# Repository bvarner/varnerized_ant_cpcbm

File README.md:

# Varnerized ANT Compact PCB Maker

Since first coming across the [ANT](https://www.youtube.com/channel/UCX44z-SSL7LzcB4xxgUdHHA) project, I've wanted to make one. However there are some esoteric hardware choices in the base project that seem to prioritize form over function and cost.
As a hobbiest, my primary concerns are not asthetics as much as cost and component availability.

## Varnerizations
1. Created a parametric (parameterized) reimplemenation of the [bridge & head in Fusion 360](https://a360.co/3jG9QqE). Fusion Archive and STEP export included.
2. 8MM Linear Rods & LM8UU linear bearings. 
    * Sacrificed 4mm of Y axis travel to allow for wall thicknesses to be reasonable with 15mm bores.
    * Added 1mm to the height to the left-right bridge and center bridge, added 1mm separation betweeen centers of the x-axis rails.
3. Bridge Core is now One Piece.
    * Captive M3 Hex Nuts allow the use of (3) M3x30 and (3) M3x40 screws instead of the original BOM spec for (3) M3 threaded rods cut to length.
    * Linear bearing holes are _barely_ oversized, allowing for the M3x30 screws to act as compression mechanisms to hold the bearings.
    * Expansion / Compression cut for linear bearings. M3 screws holding together the bridge act as compression points to hold the bearings snug.
4. Use of sub-mini microswitches for limit-switches. No need to purchase specific orientation limit switch modules, especially when the connections to the grbl board aren't making use of pull resistors.
5. NEMA17 Stepper Motors
    * Reinforced COREXY Mounts based upon [this design on Thingiverse](https://www.thingiverse.com/thing:3590519) eliminate the need for extra retainers from the thingiverse part.
    * GT2 belt-driven Z-Axis. [140 Tooth 2GT-6](https://www.amazon.com/140-2GT-6-Timing-Belt-Closed-Loop/dp/B014QJBVOY/ref=sr_1_2?dchild=1&keywords=GT2-140+belt&qid=1634881957&qsid=135-9090533-9887601&sr=8-2&sres=B014QJBVOY%2CB014SLWP68%2CB07B5ZQY4W%2CB096D4NTVR%2CB07MWDMBWK%2CB01HM6DIA8%2CB07X9CHY23%2CB07KK86NYX%2CB0897CJKS1%2CB01IPYNQT4%2CB01E91K4N8%2CB08BJ2G2X6%2CB00XR0YJIO%2CB08974S1CC%2CB07JKT5BZQ%2CB00OZDJTKK) allows for swapping out gear ratios to adjust for different leadscrew pitches.
6. TR8 Leadscrew (with 8mm pitch) for Z-Axis
7. Remodeled and removed unnecessary holes from the bridge left and right.
8. Belt holder holds a captive nut to secure it to the bridge.
9. Easily Obtainable [D2826 1000kv](https://www.amazon.com/dp/B089YPSYD6?psc=1&ref=ppx_yo2_dt_b_product_details) BLDC motor.
    * 3d-printed TPU (shore 95A) drive belt.
    * 3d-printed PolyCarbonate drive pulleys. (Eliminated the stop-collar on the spindle)
10. Use of an open cable chain, and necessary mounts to the bridge & electronics case.
    * Use of 40mm screws on the electronics case, further customizations to make it easier to fit panel-mount through-hole jacks.
    * modified the electronics panel to use a rectangular switch and a XT-60H connector for power.
11. 3d printed GT2 pulleys.
    * I have since switched to machine pulleys, as I was diagnosing some movement precision issues. Changing to machined pulleys had no noticeable effect. My issues were elsewhere.
12. PCBLock <-> Frame connection.
    * Changed orientation of the contact strips to vertical -- allowing for more 'slop' between alignment in both the x, and z axis.
    * Contact is no longer dependent upon the thickness of the spoil-board, so thinner / thicker board will still contact well.
    * I used 4mm strips of 0.15mm thick nickel strip. (cut from an 8mm wide strip commonly used in 18650 battery packs)

### Analysis and Evaulation Guidelines

In making my decisions about what to 'Varnerize' vs. purchase and stick to the plans I weighed things based upon:

* What's already in my component drawers or easily obtainable given current supply chain and production limitations. Prioritized functional available parts over form.
* What I can reasonably 3d-print and combine with something else already in my component drawers. Prioritized self fabrication over purchasing produced parts.
* Functional Accuracy. Modifications will prioritize accuracy over workable size. I was willing to reduce the work area. I didn't have to.
* Build cost.

### Specific investigations undertaken

* NEMA17 steppers in place of the NEMA11s, and in the case of the head, in place of the NEMA 8. I've seen [this top-mounted NEMA 11 modification](https://jplattel.nl/post/2021-03-07-improving-the-ant-head/) which has supplied a surprising amount of 'idea fuel'.
* Bridge segmenting and joinery.
* Use of an Arduino Uno R3 + GRBL board instead of the STM32 based Arm board + GRBL board.
* 8mm Rods and LM8UU bearings instead of the 6mm rods and LM6UU bearings.
* 3d printable pulleys based around 683ZZ bearings. As of 10/2021 I was able to obtain a 20 pack of these bearings for $10. Sourcing the appropirate number of 16-tooth pulleys would have cost more than the 20 pack of bearings.
* Overhangs in some parts (which seem to be dimensionally important) should have 'snap-off' supports.
* Use of a TR8x8 leadscrew, along with a GT2 closed loop belt and pulley system for Z-Axis motion. I have a few of these belts laying around from converting my prusa-style printer to a [Skelestruder](https://jltxplore.dozuki.com/c/Skelestruder_for_Prusa_MK3) extruder.

### Purchased items I did not 'skimp' on:
* MakerBeam! I bought the starter kit, and the tee nuts. I _did_ investigate printing the tee nuts and had workable facimilies printed with a 0.4mm nozzle but was not confident about the long-term use of the plastic tee-nuts.
* Linear rails. Experience from building 3d printers told me this was worth it.
* LM8UU Drylin Bushings. Because LM8UU ball bearings that are affordable are rubbish. I've been using drylin on my 3d printer for a year or so now, and it's so much quieter, and has so much less lash that it's just worth it.
* Mochu angular contact bearings & CL6-ER8M spindle.

#### Z-Axis Comparative Analysis
##### NEMA 8 ANT Head
The "Beta" NEMA 8 stepper head design uses a 1.8-degree, 18mN/m (0.018N/cm) holding torque stepper paired with a 4mm leadscrew with a 0.635mm pitch, equating to a 0.003175mm linear resolution per step.
(0.635mm / 200 steps = 0.003175mm). 

The default configuration is to set this to half-stepping, doubling the default ANT resolution to:
(0.635 / 400) = 0.0015875mm

##### NEMA 17 Varnerized Head
I have on hand several 17HS4401 steppers, which are 1.8-degree, 42N/cm holding torque, and TR8x8 leadscrews with 8mm pitch and anti-backlash nuts.
Un-reduced, this equates to a linear resolution of 0.04mm.
(8 / 200 = 0.04mm) 

In order to increase the resolution, I've selected a 16:52 gear ratio and 140 tooth GT2 timing belt (which I had on hand from building a Skelestruder extruder for my printer).
This brings the effective resolution to:
(8 / (200 * 3.25)) = 0.012307692mm

Enabling 1/4 stepping on the Z-axis motor brings this to:
(8 / (200 * 3.25 * 4)) = 0.003076923mm -- slighty better than the half-stepped NEMA 8.

Enabling 1/8 stepping on the Z-axis will yield:
(8 / (200 * 3.25 * 8)) = 0.001538462mm resolution -- on par with the half-stepped NEMA 8 head.

This equates to a theoretical steps/mm setting of: ~650 steps/mm

Assuming a loss of torque of 29% at the motor shaft (due to microstepping):
At the mottor shaft, the motor provides 29.82N/cm of holding torque.
(42 - (42 * 0.29))
At the lead-screw, this would be 3.25 times higher.
(29.82 * 3.25) = 89.46N/cm

**Conclusion**:

__With 1/8th microstepping, a 1:3.25 gear ratio, and an 8mm pitch leadscrew powered by a 17HS4401 NEMA17, we will exceed the repeatable resolution and torque of the ANT's NEMA8 head design.
Furthermore this part selection will enable using parts I have on hand, cutting the cost to build the head unit considerably.__

## Original ANT Project resources

[{height=50 width=20}](https://www.youtube.com/channel/UCX44z-SSL7LzcB4xxgUdHHA)  

The Ant is a project to develop a CNC machine able to realize single and double-layered printed circuit boards.

[Here is a video presentation](https://youtu.be/nVkbG-CYaAA)

The CNC machine is designed to achieve well-determined characteristics:

- Compact
- Low-cost
- Robust
- Scalable
- Easy to build
- Open License

To achieve these properties the following design principle have been adopted:

- Electrical, mechanical and electronics parts have been chosen to be small, low-cost and easily available on the open market or 3D printable
- Mechanical design has been oriented to minimize the space occupied by the components
- Mechanics has been designed to be robust and stress resistant
- Mechanics has been designed so that the external dimensions of the machine may be changed with a minimal change of pieces and no re-design needed.
- Mechanical and electrical designs have taken in account the assembling and disassembling operations, allowing to use easily available tools as screwdrivers, Allen wrenches and a solder for electrical contacts.
- The microcontroller board used to control the CNC machine is inexpensive (~15 $) but is equipped with a powerful STM32 processor and many peripherals.
- The machine control firmware can be loaded with almost no effort, since the microcontroller board has been chosen to have an on-board programmer.
- The control firmware is derived from GRBL v.0.9j, but it is also customized to achieve better performance, taking advantage of the powerful processor, and to be more flexible, since more configuration parameters and features have been added respect to the original firmware

The Ant is an open project, but if you feel like donating a small sum, you are very welcome. Just use the paypal button below.

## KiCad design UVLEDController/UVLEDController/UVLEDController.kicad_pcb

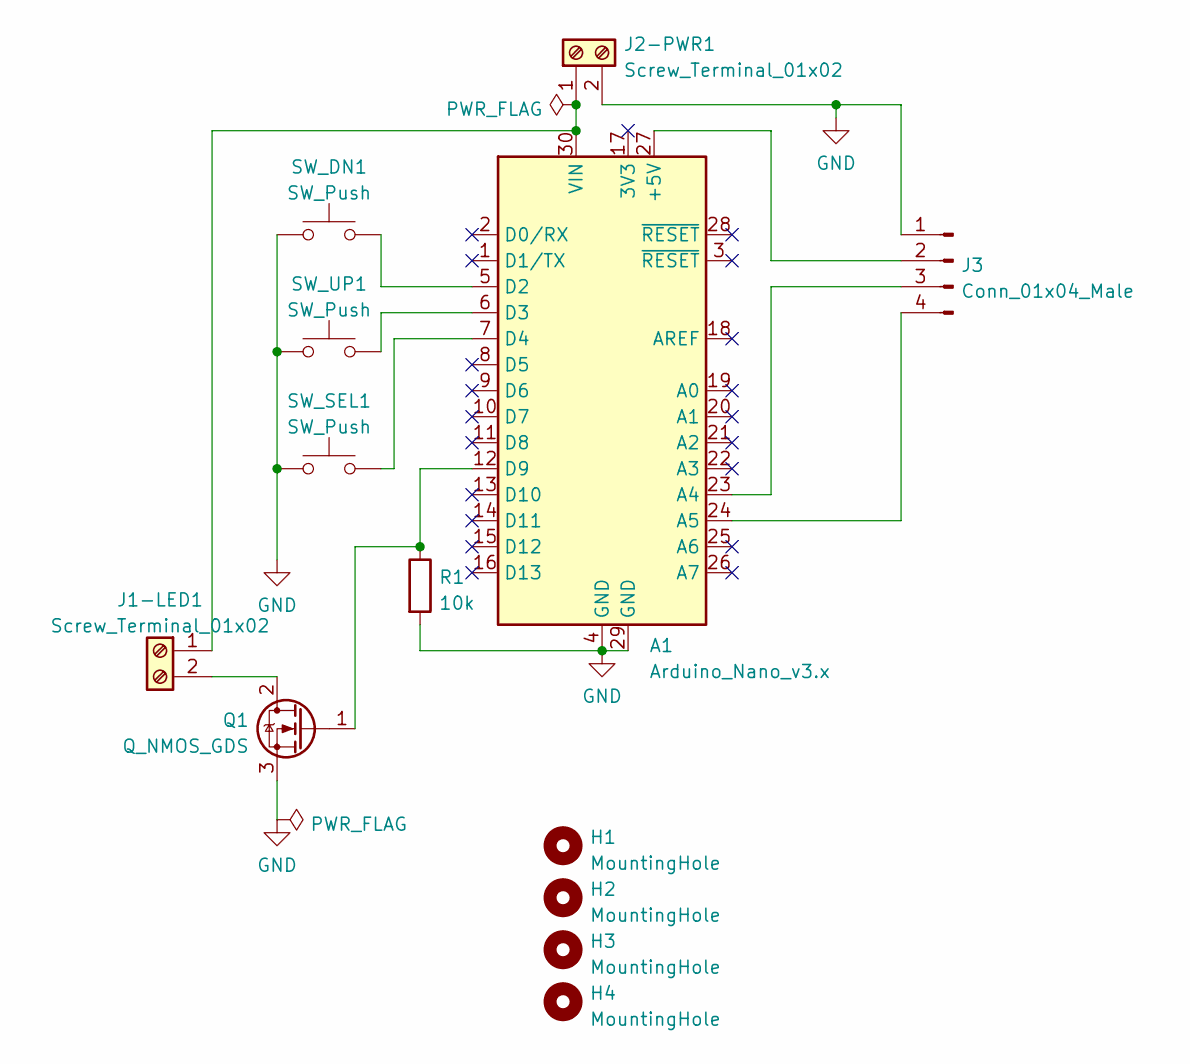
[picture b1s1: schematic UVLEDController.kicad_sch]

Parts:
A1: Arduino_Nano_v3.x; Arduino_Nano
H1, H2, H3, H4: MountingHole; MountingHole_3mm
J1-LED1, J2-PWR1: Screw_Terminal_01x02; TerminalBlock_Phoenix_PT-1,5-2-5.0-H_1x02_P5.00mm_Horizontal
J3: Conn_01x04_Male; PinHeader_1x04_P2.54mm_Horizontal
Q1: Q_NMOS_GDS; TO-220-3_Horizontal_TabUp
R1: 10k; R_0805_2012Metric_Pad1.20x1.40mm_HandSolder
SW_DN1: SW_Push; SW_PUSH_6mm
SW_SEL1: SW_Push; SW_PUSH_6mm
SW_UP1: SW_Push; SW_PUSH_6mm

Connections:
GND: A1.4 (GND), A1.29 (GND), J2-PWR1.2, J3.1, Q1.3 (S), R1.2, SW_DN1.1, SW_SEL1.1, SW_UP1.1
unnamed: A1.5 (D2), SW_DN1.2
unnamed: A1.6 (D3), SW_UP1.2
unnamed: A1.7 (D4), SW_SEL1.2
unnamed: A1.12 (D9), Q1.1 (G), R1.1
unnamed: A1.23 (A4), J3.3
unnamed: A1.24 (A5), J3.4
unnamed: A1.27 (+5V), J3.2
unnamed: A1.30 (VIN), J1-LED1.1, J2-PWR1.1
unnamed: J1-LED1.2, Q1.2 (D)

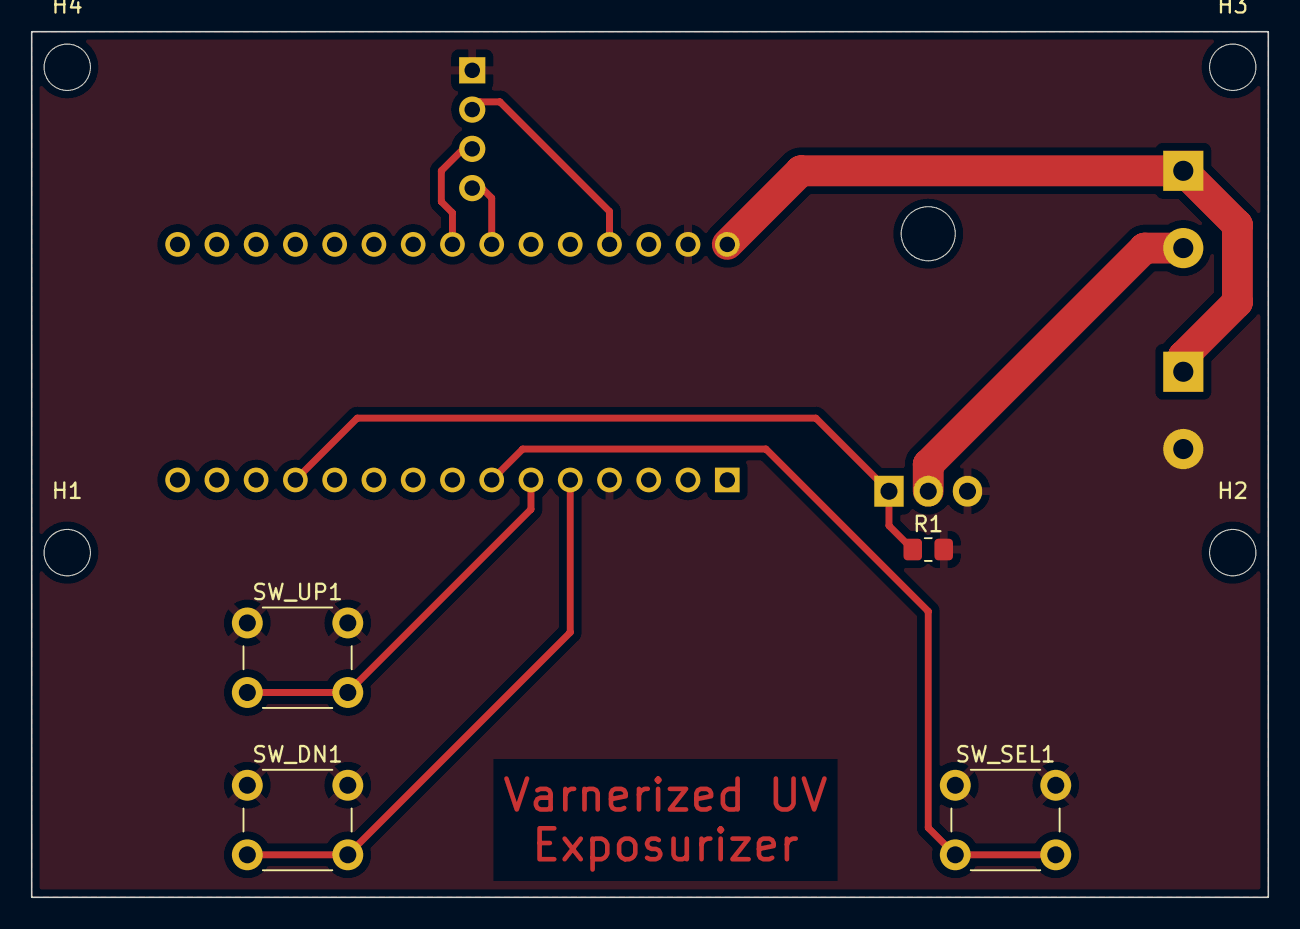
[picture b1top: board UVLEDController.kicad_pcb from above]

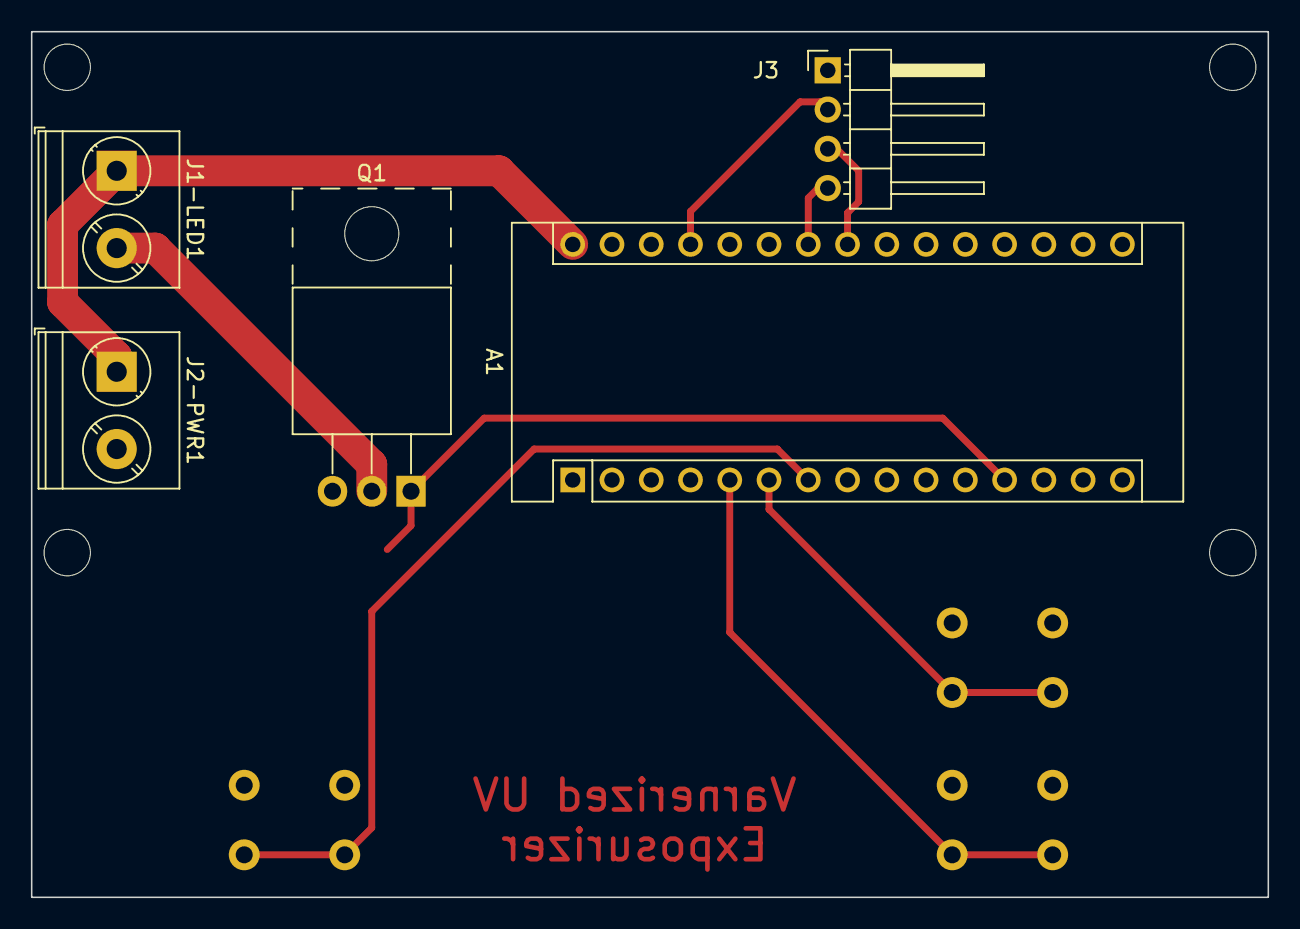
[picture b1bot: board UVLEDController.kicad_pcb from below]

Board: 2 copper layers, 80.0 x 56.0 mm, 13 parts (5 on the bottom side), 10 nets.

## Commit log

2019-04-14 Modified Connection Scheme presentation.[skip ci]
2019-04-14 Small correction [skip ci]
2019-04-14 Release v1.0. All step files released, added change tool, minor bug fixing [skip ci]
2019-04-23 Added beta development folder and beta modified head 4p2 [skip ci].
2019-05-01 Disable System input interrupt control since not used at the moment.
2019-05-01 Correction of bug on limit switch debounce timer.
2019-05-08 Correction of bug. Z sign movement was not taken in account properly.
2019-05-13 Added Afro mini race spec as alternative ESC, other small BOM 1.0 corrections. [skip ci]
2019-05-13 Correct wrong axis sign in system position after homing.
2019-05-15 ESC bullet connectors note[skip ci]
2019-05-20 Removed a compilation warning.
2019-06-08 Added Reddit link [skip ci]
2019-06-16 Correcting suggestions in mechanical Release Notes.
2019-07-21 Improved versions of Head and Bridge added in mechanics release folders. [skip ci]
2019-07-22 New fw files organization and configurable compile script [skip ci]
2019-07-23 Pipeline script modified to compile from configurable script.
2019-07-23 Correction of build script
2019-07-23 Give execution permit to the compile script.
2019-07-23 Test deployment
2019-07-23 Adding override to CFLAGS.
2019-08-24 Specified use of 16 and 26 AWG cables. [skip ci]
2019-08-26 Correct bug on STEP_MASK
2019-08-28 Heuristic correction of freeze Usart bug after an hold and stop. Cause still to be investigated.
2019-09-29 Added Cutterpillar design files and related info.
2019-09-29 Edit Release_Notes [skip ci]
2019-09-30 Files moved to cutterpilla folder.[skip ci]
2019-11-15 EXTI CLEAR masks correction
2019-12-01 Correction on spindle stop function, the pwm output is frozen to zero, instead of disabling it (high impedance state)
2019-12-01 Added heartbeat functionality
2019-12-01 Added missing mod for the heartbeat
2019-12-01 -Added heartbeats'led on PA5, spindle dir moved to PA12 -Doubled sizes of block buffer -Increased sizes of tx and rx serial -serial variable from 8 to 32 bits -nmi and hard fault handlers have faster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
2019-12-15 Added simple PCB Test [skip ci].
2019-12-24 Adding Solder Mask Add-On part. [skip ci]
2020-01-09 Changed memory linking and location of parameters in smaller flash sectors.
2020-01-12 New PCB Holder design files in beta [skip ci]
2020-01-18 Correction of pdf files for pcb lock 2.0[skip ci]
2020-01-18 Untrack unuseful file from firmware [skip ci].
2020-01-22 BOM for the new PCB holder [skip ci].
2020-02-01 Setting minor version as 9, to recall 0.9 grbl version.
2020-02-01 Added firmware release note [skip ci]
2020-02-09 Specified JST PH 2.0 in the BOMs files. [skip ci]
2020-02-09 Added important note on tags and release notes in the BOMs files. [skip ci]
2020-02-11 Adding gap-fill option to avoid zeros in between sections and in the settings space.
2020-02-11 Adding release notes for 0.9.58 [skip ci].
2020-03-11 Added homing debug setting $95. If $95 is set to 1, the GRBL controller sends debug strings during homing.
2020-03-12 Updated release note for version 0.9.59. [skip ci]
2020-03-14 First GRBL1.1 experimental release.
2020-03-14 Ignore eclipse settings files [skip ci].
2020-03-27 Updated Firmware Release Notes for version 1.1.60 [skip ci].
2020-05-18 Set PWM OFF value as spindle_pwm_min_time_on.
2020-05-19 Setting minimum PWM instead of disabling if pwm spindle speed is set to 0.
2020-05-20 Updated Firmware Release Notes. [SKIP CI]
2020-07-18 Removed blocking loop not needed in version 1.1.
2020-07-18 Removed unused function.
2020-08-13 Improved robustness of serial communication.
2020-08-15 Small correction of indentation [skip ci].
2020-08-17 Added second section of code in ram (ramcode2), moved protocol, report settings and system code in this zone. Moved heartbeat led ddr settings before other initializations.
2020-12-25 Squaring feature, experimental code [skip ci].
2020-12-27 Modified heartbeat led initialization. [skip ci]
2020-12-27 Changing authors in file header. [skip ci]
2020-12-28 Implemented PWM spindle ramps for CNC machining. Laser behavior unchanged.
2021-02-06 Moved betas accepted or substituted to old_beta_developments folder. [skip ci]
2021-02-06 New HEAD with NEMA8 motor, pcb lock, bridge_b and cable chain. [skip ci]
2021-05-22 Fixed STL.
2021-06-02 Ramping avoided if the new pwm is equal to current pwm.
2021-10-18 Prepping for work.
2021-10-18 Modified the right and left bridge to use an 8mm rod.
2021-10-18 Upper bridge 8mm beam repositioned 1mm up, to make room for the belt on the right side.
2021-10-18 Updated some docs. NEMA 17 Motor mount. Mirror for other side.
2021-10-19 Pushing updates to start print analysis.
2021-10-19 First attempt at GT2 Pulleys using 683ZZ bearings. Checking in a few 3mf projects that I'll be testing as well.
2021-10-20 After a few tweaks, the GT2 pulleys seem to work. Need to rename the files.
2021-10-20 Renamed the files since I have a mental block on how pulley is spelled.
2021-10-20 Documented the NEMA7 Mount.
2021-10-20 Bridge Core Test Update.
2021-10-20 Added the 3mf from tuning my PETG for pulley production.
2021-10-20 * Converted all Bridge fasteners to pocketed M3 hex nuts, rather than square nuts on the back. * LM8UU * Slightly larger hole size. * Cutout for flex expansion / compression around bearings. The M3x3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
2021-10-20 Updating the readme as I go.
2021-10-20 Updating print settings.
2021-10-20 One more thing to look into
2021-10-21 Update to the shim washer for the pulleys.
2021-10-21 wording.
2021-10-22 Update to the pulley washer to use the outer diameter specificed by the ANT project.
2021-10-22 * Parametric bridge bottom cap modifications. :-)
2021-10-23 * Updated the bridget bottom cap to use better constraints now that I understand sketches better. :-) * Designed a new head for use with a D-Power Series D2826 1000KV motor, and TR8 leadscrew with to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
2021-10-23 3mf for the bridge bottom
2021-10-23 * Core bottom: added a few fillets to match the core. * Core: Added fillets to improve printability when rotated to maintain proper diameter for the LM8UU bearings. * Head: Fitment fixes * Adjusted p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
2021-10-23 Mirrored the NEMA mounts.
2021-10-26 PARAMETRIC, CONSTRAINED CAD MODELS FOR THE WIN!
    No really, re-implemented the bridge and head assembly in Fusion360 as parametric models. So awesome. Much Wow.
    So this is the first STL dump of that work, which sets up the head to use an inexpensive D2826 BLDC and TR8x8 leadscrew on a 1:3.5 reduction driven from a NEMA17 mounted up top.
2021-10-26 * Y-axis bridge parts * Fixed spacing issue for mount hole locations. * Corrected the lack of counterboring. * Adjusted orientation of the M3 nut cutout for the idler bearings. * Fixed small issue on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
2021-10-26 * Fitment adjustments of M3 nut pockets.
2021-10-26 Adding the export.
2021-10-27 Adding projects for printing things.
2021-10-28 Improved the room for the NEMA head mount hex nuts. I was able to use the first printed head by heating up square nuts and melting them into position.
2021-10-28 Refinements for Fit.
    * Bridge core modifications based on print output.
    * bridge nema_17 rotation angle for tension adjusted (added 5 more degrees) of rotation.
    * Bridge upper embedded nuts modified to proper thickness for M3 hex nuts.
2021-10-28 Updates to the z-axis drive pulleys.
2021-10-28 Fixed a missing face for an extrude.
2021-10-28 * Adjusted the wire escapement for the z-limit switch.
2021-10-29 Added a 48 tooth pulley, since the 56 is a bit... too big.
2021-10-29 Adding a 50-tooth pulley, which should fit better for the 140 tooth belt lenght, and 1:3.125 gives an even number of steps/mm that doesn't end with a non-repeating decimal for fractional depths. :-)
2021-10-29 Updated the README with the calculations for the Z-axis design.
2021-10-29 * Added a spacer for the GT2 drive pulley on the z-axis, so that it can bear against the upper and lower bearings. * Added 6mm height to the upper bridge to compensate for the necessary 6mm added to 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
2021-10-30 * Updates to the head to completely encase the LM8UU bearings. * Auto increase the upper bridge height to compensate for different linear bearing lengths. * Adjust position of the outrunner motor bas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
2021-10-30 Fixed the missing bearing / shaft bore in the head, and moved the Z-nut back down to 4mm.
2021-10-31 Updates on print files.
2021-11-02 initial pass at a y-limit switch mount
2021-11-03 moved it a bit.
2021-11-03 Adding a panel mount XT60
2021-11-03 Updating to match the UNO R3 modifications.
2021-11-03 Cleanup
2021-11-03 Varnerized.
2021-11-05 Adjust the back electronics housing for an UNO R3, and make it M3x40 friendly. Remove the firmware. I'm storing that in a separate repo.
2021-11-05 Added the cable chain parts.
2021-11-05 Updates for the cable chain.
2021-11-05 Fixes for the bridge anchor.
2021-11-06 Intermediate re-organization of mechanical folder: copied parts file from beta development, removed old versions. Missing BOM updates and other modifications. [skip ci]
2021-11-06 Intermediate re-organization of mechanical folder: changed pcb_lock_brass_foil_jig and updated version of bed holder with one part that is now in pcb_lock_frame_to_bed_connection_1p0. Missing BOM upd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
2021-11-06 The_Ant_version_1_1_0 release [skip ci]
2021-11-07 Motor and shaft pulley changed.
2021-11-07 Make it not move.
2021-11-07 Resized the mount holes.
2021-11-08 Adjustments for the motor and shaft pulley
2021-11-08 Added drive belts.
2021-11-09 Drive belt redesign and upper bridge tweak.
2021-11-09 Adding some extra belt diameters.
2021-11-09 Updates to the readme.
2021-11-10 Some readme updates.
2021-11-10 Added zip tie points to the cable chain mount.
2021-11-13 Drive Belt changes, Head probe screw adaptation.
2021-11-14 Added some Feet. Totally cribbing this.
2021-11-14 Added a bed bracket system.
2021-11-14 Updated to give a bit more space for the nuts to enable sliding, and to move the conductor holes in the hold-down.
2021-11-15 Fixed the right bracket lack of counterbore
2021-11-19 Rather Major update to address some fitment issues.
    * 5.5mm camera clamp. Parameter added.
    * Moved the z-axis nut and screw position to no longer interferre with the camera.
    * Added a 30mm screw to help clamp the z-axis motor mount and bridge together, resisting upward motion of the z-axis.
    * Made the bridge and motor mount a bit more stiff around the 22mm bearings to help resist vertical motion.
    * Revised the sketches for a few components to better constrain them.
    * The head's limit-switch screw hole should be able to recess now.
2021-11-19 Found some missing geometry on the head.
2021-11-19 Forgot it exports in 3mf by default. Yick.
2021-11-21 * Camera offset now 15x5, to avoid interference between the clamp and the spindle belt. * Fixed a missing volume in the upper bridge.
2021-12-10 Modified logo image link. [skip ci]
2021-12-13 The_Ant_version_1_1_0 release fixed. [skip ci]
2022-02-15 Adding a re-do of the frame to pcb lock connections. Vertical orientation, wider stuff, integrated LED & resistor mounts.
2022-02-15 Tweaks to fitment.
2022-02-16 Updates to the bed-side connection.
2022-02-21 Some minor adjustments to the readme.
2022-02-21 The varnerized pcb_lock to bed_frame.
2022-02-21 Added some documentation.
2022-02-21 Include public links.
2022-06-25 A Picture is worth a thousand words, right?
2022-07-02 UV Controller Board.
2022-07-02 Added the plots.
2022-07-02 Updates for physical dimensions based on Fuseion360 test fits.
2022-07-02 Moved the buttons to below the screen.
2022-07-02 Moved the screw terminals to a better location. Tweaked position of i2c header.
2022-07-07 Rotated.
2022-07-12 MOved the drill and place offset.
2022-07-15 Modifications for mounting / creating a cabinet to sit beneath the Varnerized ANT. * UV Curing bay. * Intensity (PWM) & Timer controlled by Arduino. * PSU Shroud Holds all circuitry. * KiCad project 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
2022-07-20 Remove the backups.
2022-08-10 Just making sure these are here...
